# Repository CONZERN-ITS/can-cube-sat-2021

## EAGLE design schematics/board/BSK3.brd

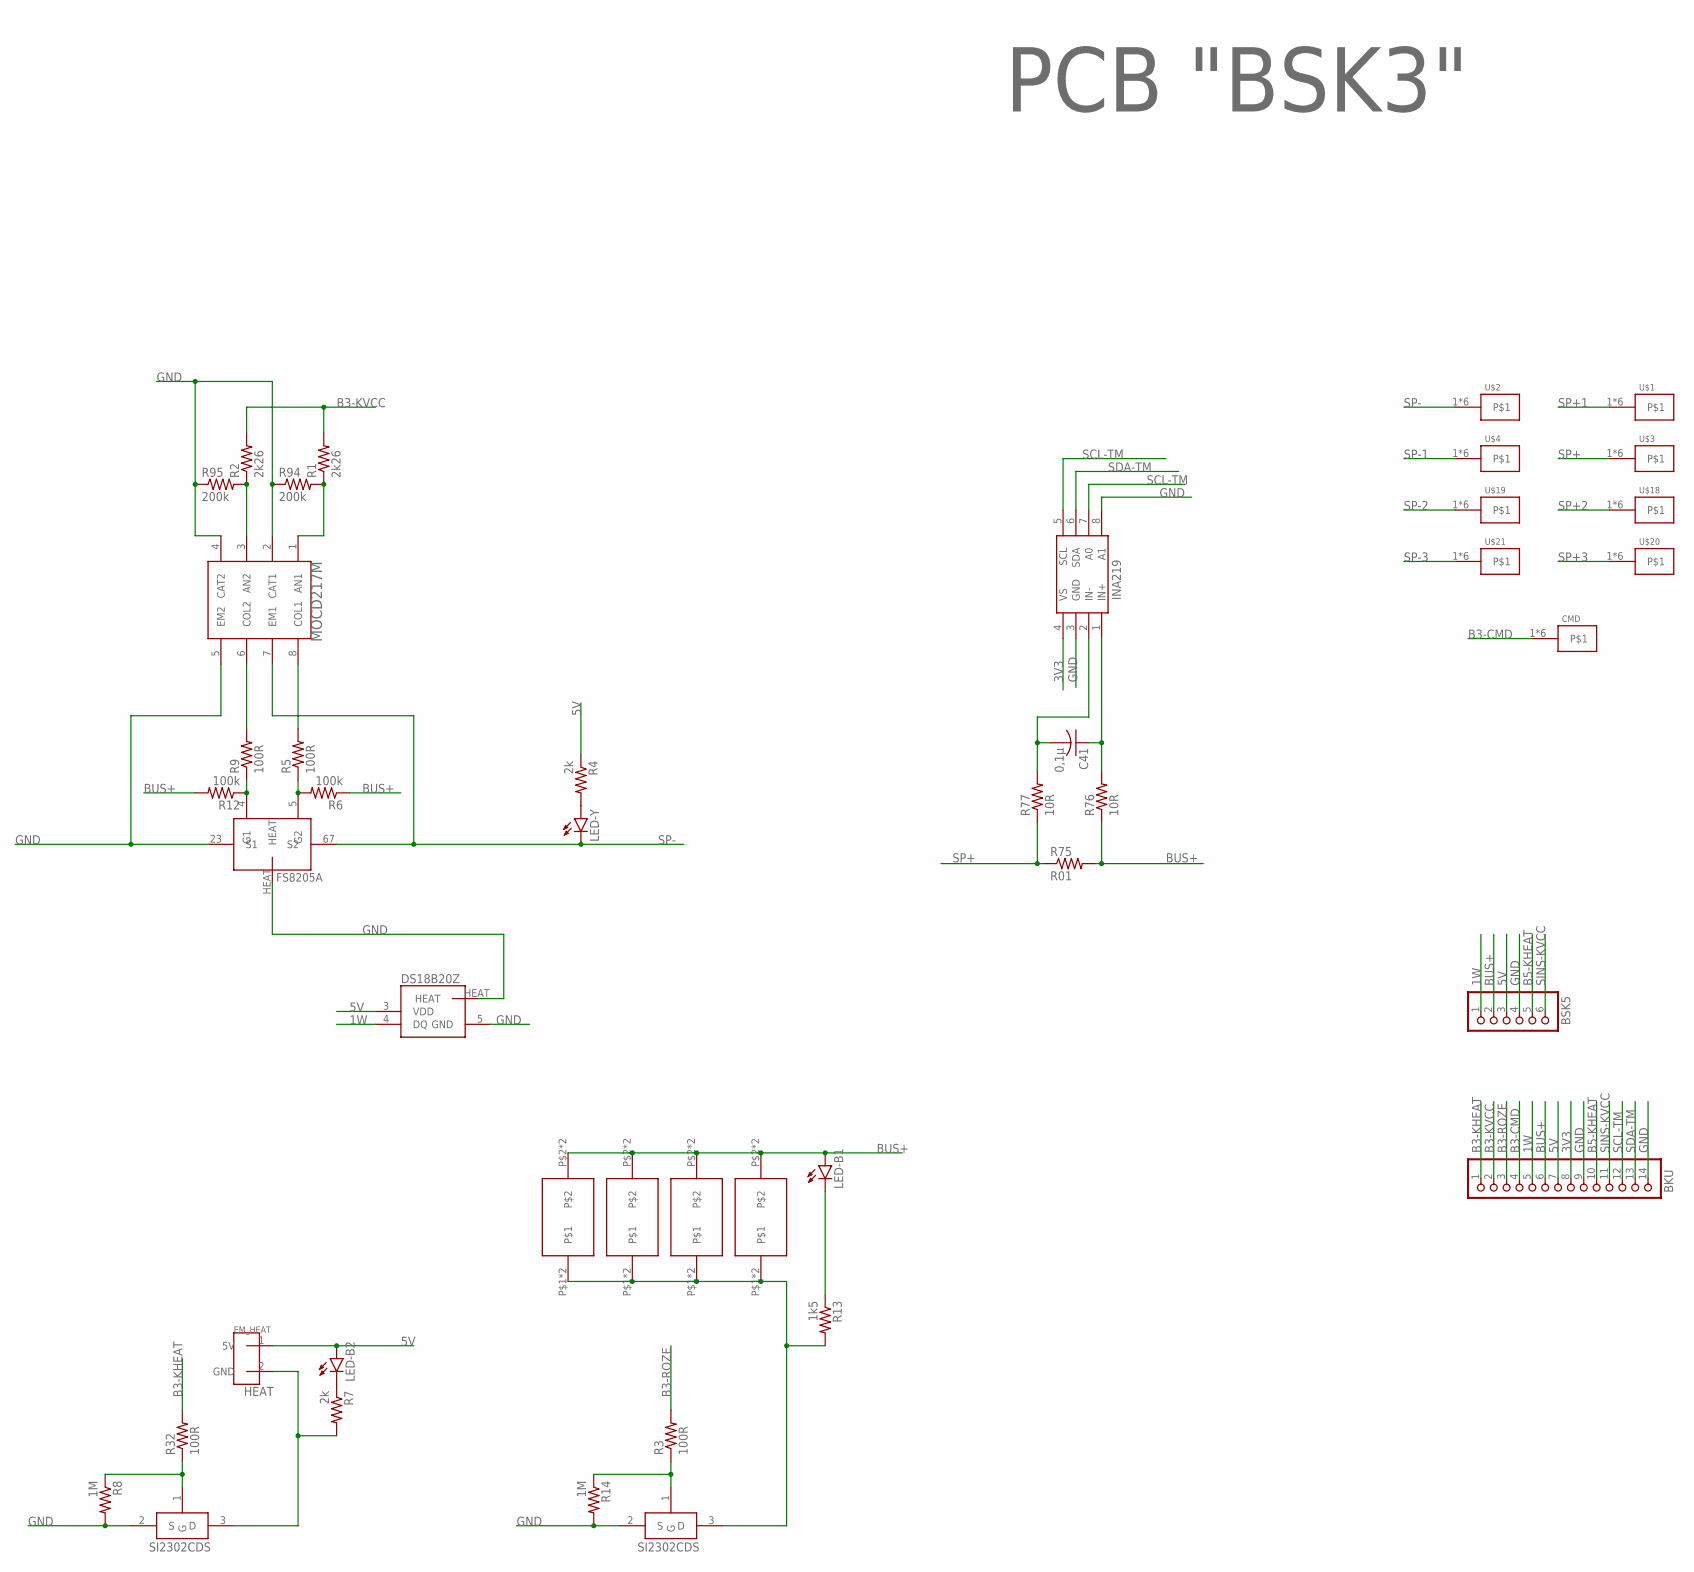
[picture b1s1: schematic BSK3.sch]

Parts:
BKU: PINHD-1X14; 1X14
BSK5: PINHD-1X6; 1X06
C41: 0,1µ; C0603
CMD: KCONNECTQUAD; KCONNECT_QUAD
DS18B20Z: DS18B20Z; SOIC8+HEAT_S
INA: INA219AID; SOT23-8
LED-B1, LED-B2: LEDCHIPLED_0603; CHIPLED_0603
LED-Y: LAP4-BOTTOM; P47F-BOTTOM
R1, R2: 2k26; R0603
R3, R5, R9, R32: 100R; R0603
R4, R7: 2k; R0603
R6, R12: 100k; R0603
R8, R14: 1M; R0603
R13: 1k5; R0603
R75: R01; R2512
R76, R77: 10R; R0603
R94, R95: 200k; R0603
U$1, U$2, U$3, U$4, U$18, U$19, U$20, U$21: KCONNECT
U$5: MOCD; SOIC8
U$6, U$7, U$15, U$16: GRAFITGRAFIT4_2; GRAFIT4_2
U$8, U$13: SI2302CDS; SOT23-3
U$9: PCB "BSK3"; ITS-LOGO
U$14: EM_HEAT
U$26: FS8205A+

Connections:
1: R7.2, U$8.3 (D), U$14.2 (GND)
1W: BKU.5, BSK5.1, DS18B20Z.4 (DQ)
2: R13.2, U$6.P$1, U$6.P$4, U$7.P$1, U$7.P$4, U$13.3 (D), U$15.P$1, U$15.P$4, U$16.P$1, U$16.P$4
3V3: BKU.8, INA.4 (VS)
5V: BKU.7, BSK5.3, DS18B20Z.3 (VDD), LED-B2.A, R4.1, U$14.1 (5V)
B3-CMD: BKU.4, CMD.1, CMD.2, CMD.3, CMD.4, CMD.P$1, CMD.P$2
B3-KHEAT: BKU.1, R32.2
B3-KVCC: BKU.2, R1.2, R2.2
B3-ROZE: BKU.3, R3.2
B5-KHEAT: BKU.10, BSK5.5
BUS+: BKU.6, BSK5.2, LED-B1.A, R6.1, R12.2, R75.2, R76.1, U$6.P$2, U$6.P$5, U$7.P$2, U$7.P$5, U$15.P$2, U$15.P$5, U$16.P$2, U$16.P$5
GND: BKU.9, BKU.14, BSK5.4, DS18B20Z.5 (GND), DS18B20Z.HEAT, INA.3 (GND), INA.8 (A1), R8.2, R14.2, R94.1, R95.1, U$5.2 (CAT1), U$5.4 (CAT2), U$5.5 (EM2), U$8.2 (S), U$13.2 (S), U$26.23 (S1), U$26.HEAT
unnamed: R5.1, R6.2, U$26.5 (G2)
unnamed: R1.1, R94.2, U$5.1 (AN1)
unnamed: R2.1, R95.2, U$5.3 (AN2)
unnamed: R8.1, R32.1, U$8.1 (G)
unnamed: R3.1, R14.1, U$13.1 (G)
unnamed: R9.1, R12.1, U$26.4 (G1)
unnamed: LED-Y.A, R4.2
unnamed: LED-B1.C, R13.1
unnamed: LED-B2.C, R7.1
unnamed: C41.1, INA.1 (IN+), R76.2
unnamed: C41.2, INA.2 (IN-), R77.2
OC1: R9.2, U$5.6 (COL2)
OD1: R5.2, U$5.8 (COL1)
SCL-TM: BKU.12, INA.5 (SCL), INA.7 (A0)
SDA-TM: BKU.13, INA.6 (SDA)
SINS-KVCC: BKU.11, BSK5.6
SP+: R75.1, R77.1, U$3.1, U$3.2, U$3.3, U$3.4, U$3.P$1, U$3.P$2
SP+1: U$1.1, U$1.2, U$1.3, U$1.4, U$1.P$1, U$1.P$2
SP+2: U$18.1, U$18.2, U$18.3, U$18.4, U$18.P$1, U$18.P$2
SP+3: U$20.1, U$20.2, U$20.3, U$20.4, U$20.P$1, U$20.P$2
SP-: LED-Y.C, U$2.1, U$2.2, U$2.3, U$2.4, U$2.P$1, U$2.P$2, U$5.7 (EM1), U$26.67 (S2)
SP-1: U$4.1, U$4.2, U$4.3, U$4.4, U$4.P$1, U$4.P$2
SP-2: U$19.1, U$19.2, U$19.3, U$19.4, U$19.P$1, U$19.P$2
SP-3: U$21.1, U$21.2, U$21.3, U$21.4, U$21.P$1, U$21.P$2

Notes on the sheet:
HEAT

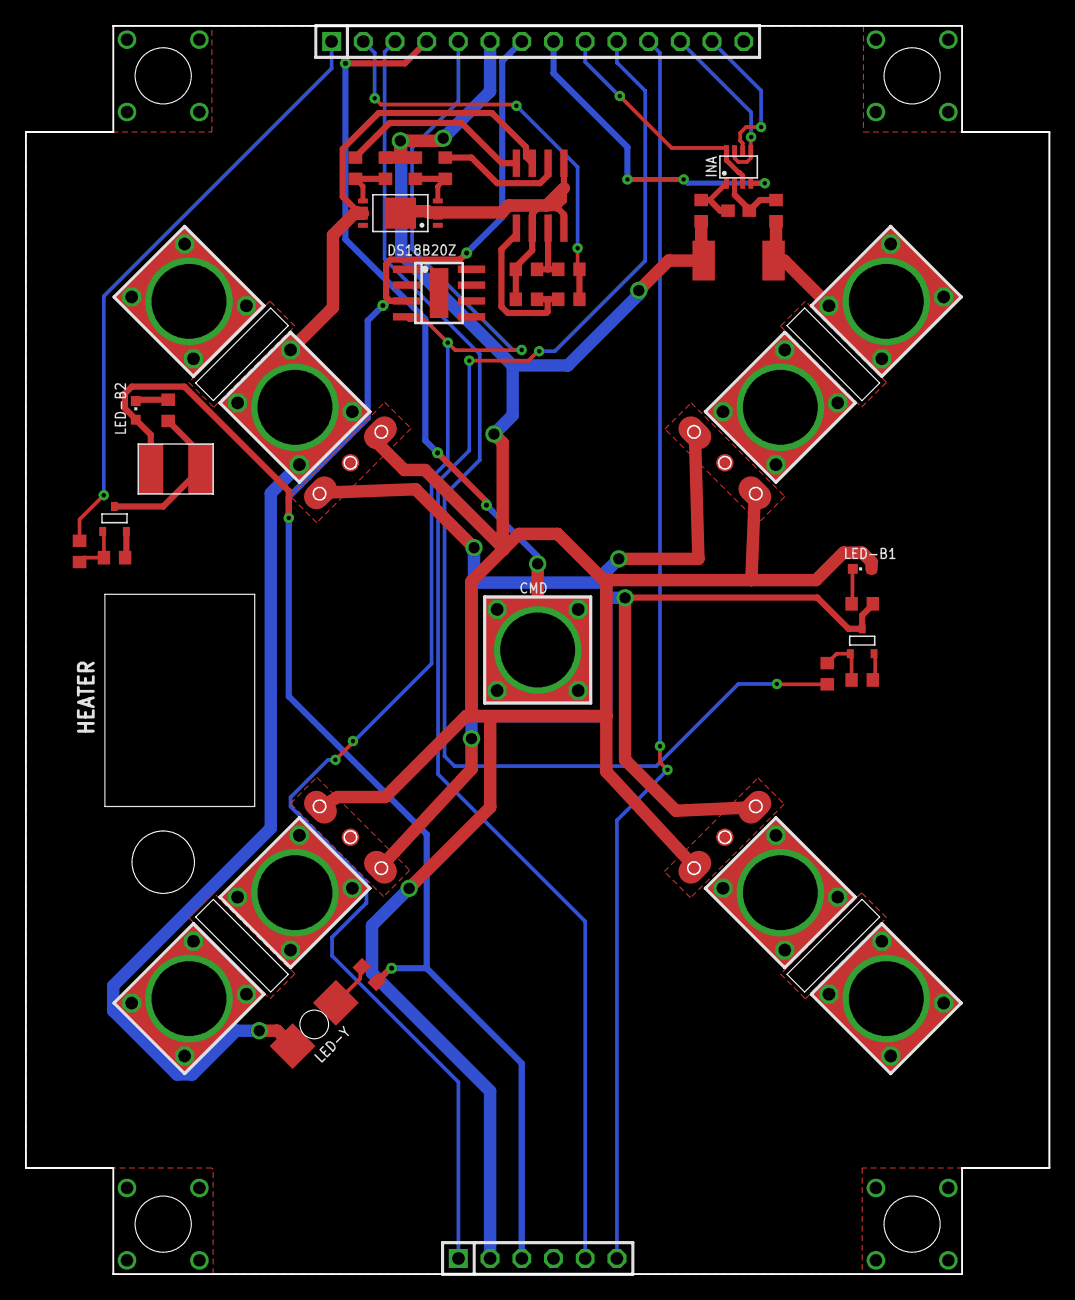
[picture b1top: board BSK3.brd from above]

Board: 2 copper layers, 82.0 x 100.0 mm, 45 parts (1 on the bottom side), 36 nets.

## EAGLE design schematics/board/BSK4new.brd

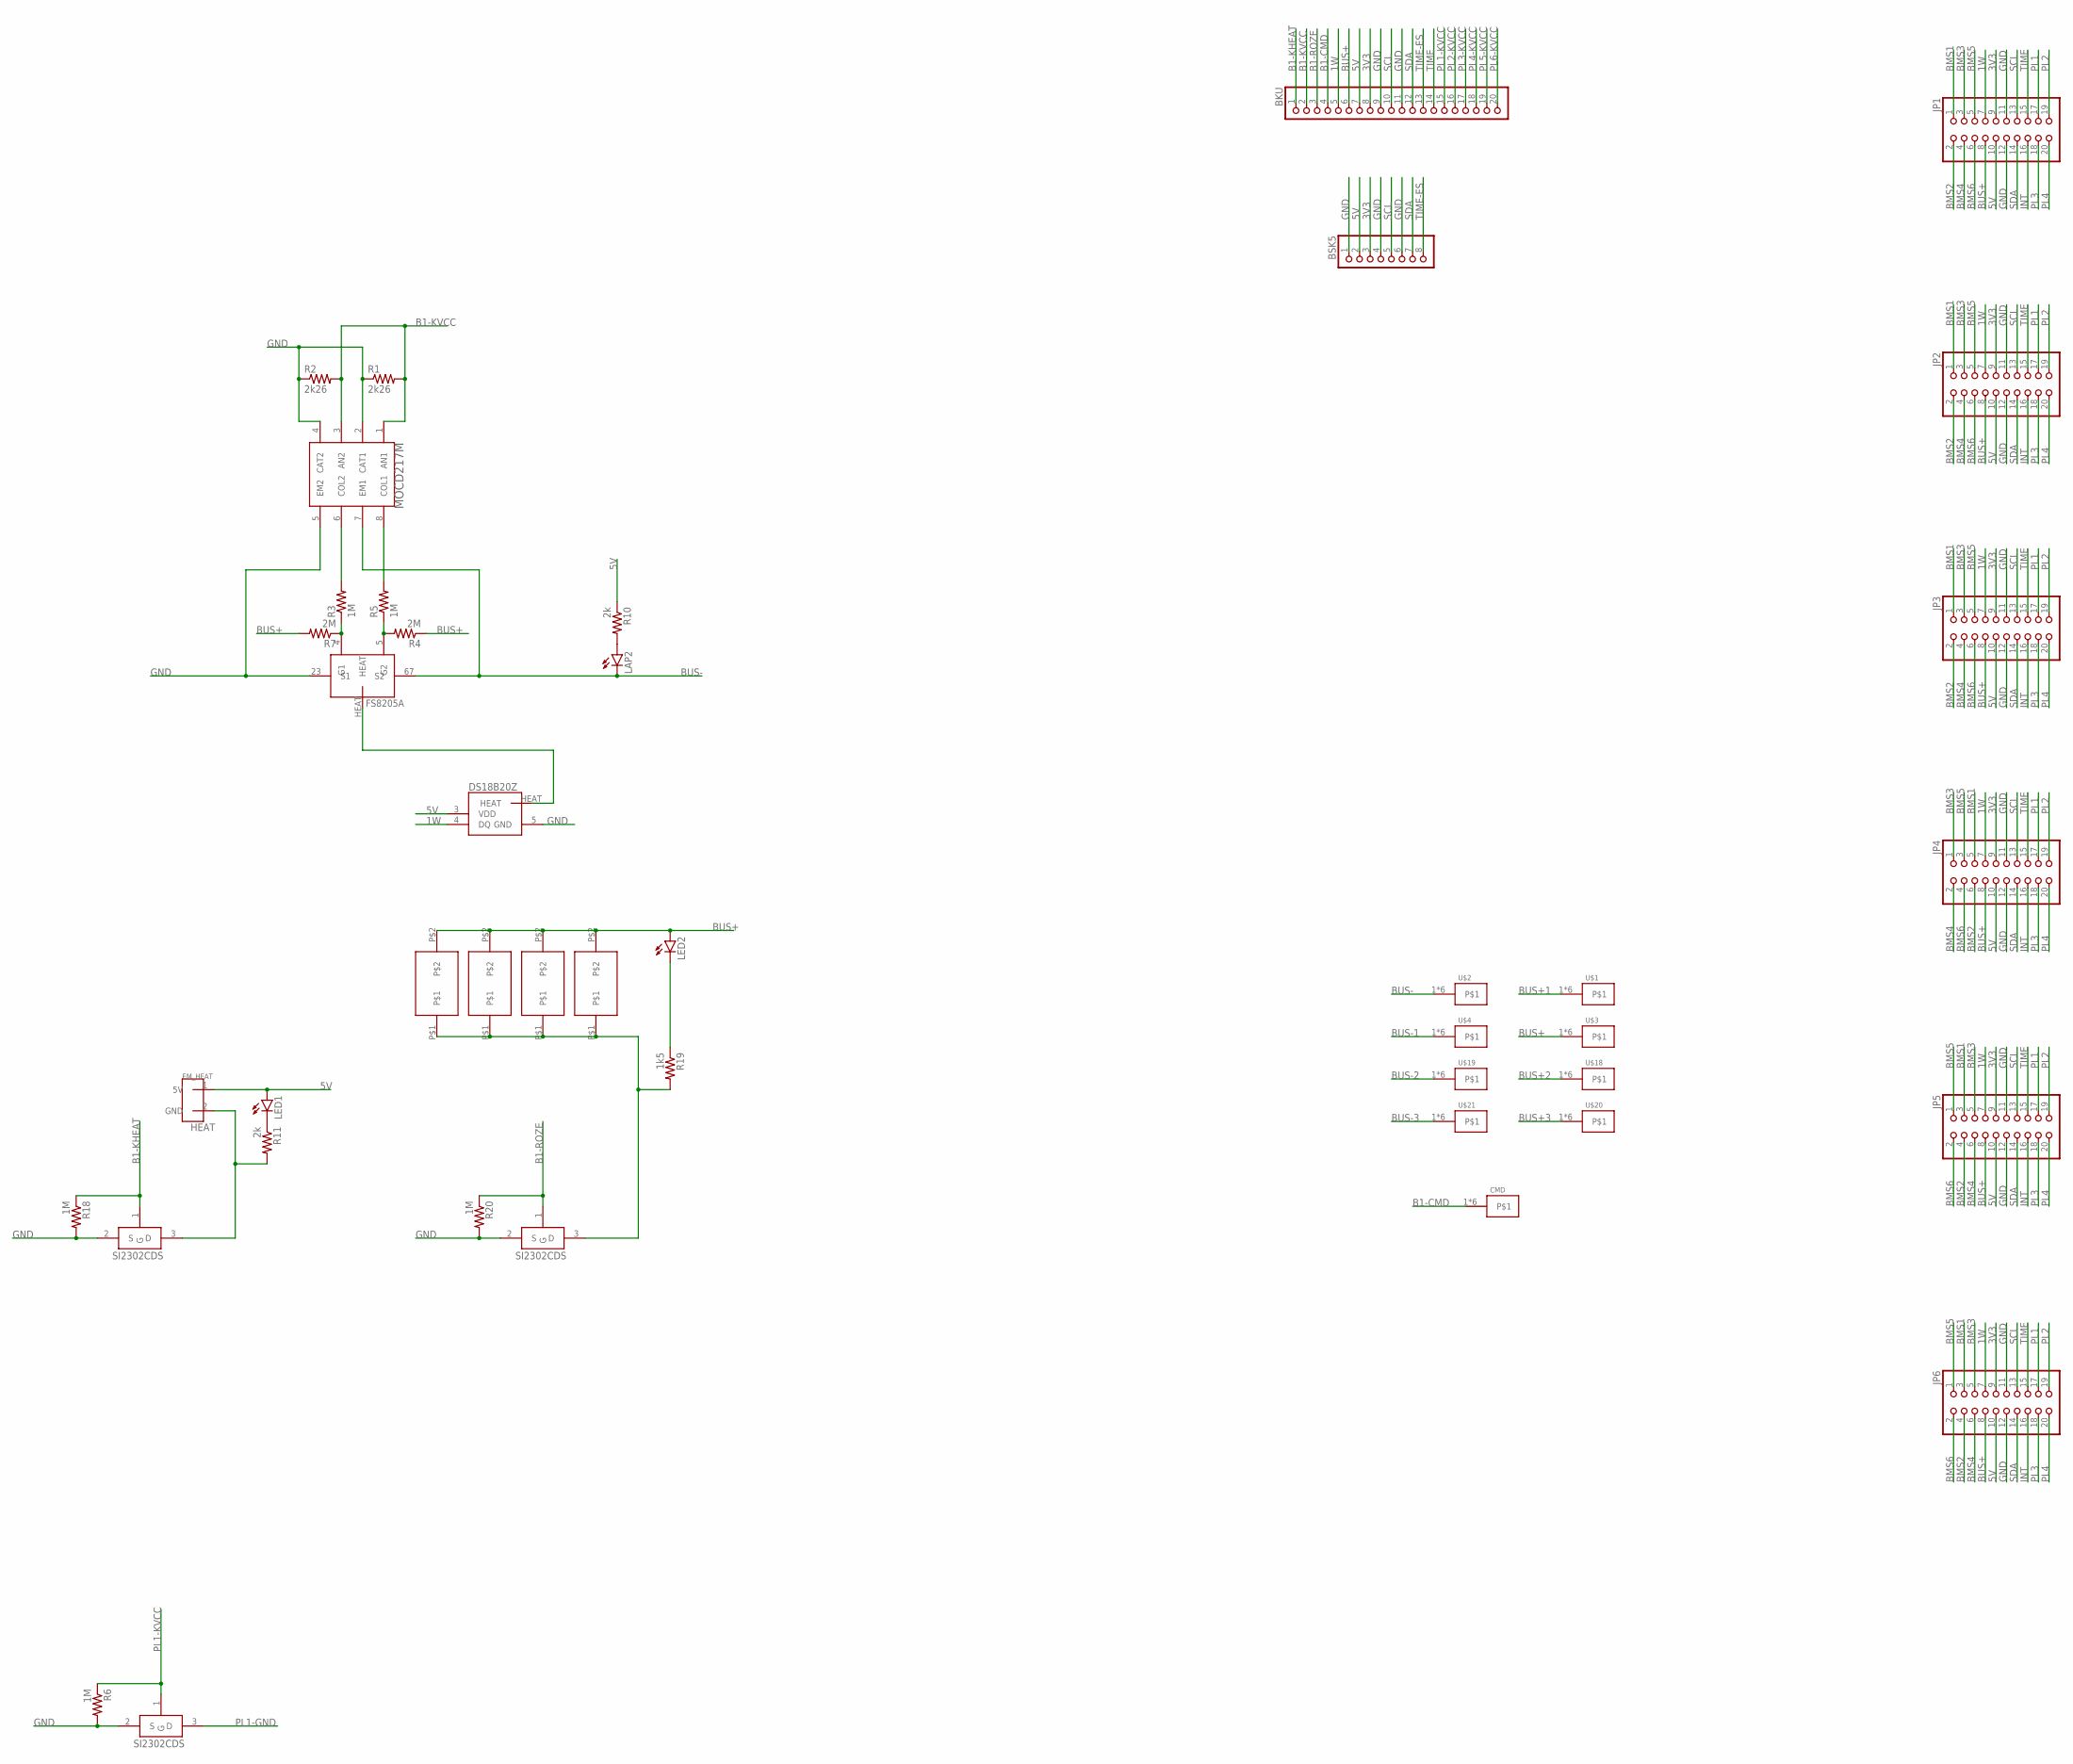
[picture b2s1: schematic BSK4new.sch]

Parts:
BKU: PINHD-1X20; 1X20
BSK5: PINHD-1X8; 1X08
CMD: KCONNECTQUAD; KCONNECT_QUAD
DS18B20Z: DS18B20Z
JP1, JP2, JP3, JP4, JP5, JP6: PINHD-2X10; 2X10
LAP2: LAP4-BOTTOM; P47F-BOTTOM
LED1, LED2: LEDCHIPLED_0603; CHIPLED_0603
R1, R2: 2k26; R0603
R3, R5, R6, R18, R20: 1M; R0603
R4, R7: 2M; R0603
R10, R11: 2k; R0603
R19: 1k5; R0603
U$1, U$2, U$3, U$4, U$18, U$19, U$20, U$21: KCONNECT
U$5, U$23, U$25: SI2302CDS; SOT23-3
U$17: FS8205A+
U$22: MOCD217M; SOIC8
U$24: EM_HEAT
U$27, U$28, U$29, U$30: GRAFITGRAFIT3_1; GRAFIT3_1

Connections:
1W: BKU.5, DS18B20Z.4 (DQ), JP1.7, JP2.7, JP3.7, JP4.7, JP5.7, JP6.7
3: R11.2, U$23.3 (D), U$24.2 (GND)
3V3: BKU.8, BSK5.3, JP1.9, JP2.9, JP3.9, JP4.9, JP5.9, JP6.9
4: R19.2, U$25.3 (D), U$27.P$1, U$28.P$1, U$29.P$1, U$30.P$1
5V: BKU.7, BSK5.2, DS18B20Z.3 (VDD), JP1.10, JP2.10, JP3.10, JP4.10, JP5.10, JP6.10, LED1.A, R10.1, U$24.1 (5V)
B1-CMD: BKU.4, CMD.1, CMD.2, CMD.3, CMD.4, CMD.P$1, CMD.P$2
B1-KHEAT: BKU.1, R18.1, U$23.1 (G)
B1-KVCC: BKU.2, R1.2, R2.2, U$22.1 (AN1), U$22.3 (AN2)
B1-ROZE: BKU.3, R20.1, U$25.1 (G)
BMS1: JP1.1, JP2.1, JP3.1, JP4.5, JP5.3, JP6.3
BMS2: JP1.2, JP2.2, JP3.2, JP4.6, JP5.4, JP6.4
BMS3: JP1.3, JP2.3, JP3.3, JP4.1, JP5.5, JP6.5
BMS4: JP1.4, JP2.4, JP3.4, JP4.2, JP5.6, JP6.6
BMS5: JP1.5, JP2.5, JP3.5, JP4.3, JP5.1, JP6.1
BMS6: JP1.6, JP2.6, JP3.6, JP4.4, JP5.2, JP6.2
BUS+: BKU.6, JP1.8, JP2.8, JP3.8, JP4.8, JP5.8, JP6.8, LED2.A, R4.1, R7.2, U$3.1, U$3.2, U$3.3, U$3.4, U$3.P$1, U$3.P$2, U$27.P$2, U$28.P$2, U$29.P$2, U$30.P$2
BUS+1: U$1.1, U$1.2, U$1.3, U$1.4, U$1.P$1, U$1.P$2
BUS+2: U$18.1, U$18.2, U$18.3, U$18.4, U$18.P$1, U$18.P$2
BUS+3: U$20.1, U$20.2, U$20.3, U$20.4, U$20.P$1, U$20.P$2
BUS-: LAP2.C, U$2.1, U$2.2, U$2.3, U$2.4, U$2.P$1, U$2.P$2, U$17.67 (S2), U$22.7 (EM1)
BUS-1: U$4.1, U$4.2, U$4.3, U$4.4, U$4.P$1, U$4.P$2
BUS-2: U$19.1, U$19.2, U$19.3, U$19.4, U$19.P$1, U$19.P$2
BUS-3: U$21.1, U$21.2, U$21.3, U$21.4, U$21.P$1, U$21.P$2
GND: BKU.9, BKU.11, BSK5.1, BSK5.4, BSK5.6, DS18B20Z.5 (GND), JP1.11, JP1.12, JP2.11, JP2.12, JP3.11, JP3.12, JP4.11, JP4.12, JP5.11, JP5.12, JP6.11, JP6.12, R1.1, R2.1, R6.2, R18.2, R20.2, U$5.2 (S), U$17.23 (S1), U$22.2 (CAT1), U$22.4 (CAT2), U$22.5 (EM2), U$23.2 (S), U$25.2 (S)
INT: JP1.16, JP2.16, JP3.16, JP4.16, JP5.16, JP6.16
unnamed: R4.2, R5.1, U$17.5 (G2)
unnamed: LED1.C, R11.1
unnamed: LED2.C, R19.1
unnamed: DS18B20Z.HEAT, U$17.HEAT
unnamed: R3.1, R7.1, U$17.4 (G1)
unnamed: LAP2.A, R10.2
OC2: R3.2, U$22.6 (COL2)
OD2: R5.2, U$22.8 (COL1)
PL1: JP1.17, JP2.17, JP3.17, JP4.17, JP5.17, JP6.17
PL1-GND: U$5.3 (D)
PL1-KVCC: BKU.15, R6.1, U$5.1 (G)
PL2: JP1.19, JP2.19, JP3.19, JP4.19, JP5.19, JP6.19
PL2-KVCC: BKU.16
PL3: JP1.18, JP2.18, JP3.18, JP4.18, JP5.18, JP6.18
PL3-KVCC: BKU.17
PL4: JP1.20, JP2.20, JP3.20, JP4.20, JP5.20, JP6.20
PL4-KVCC: BKU.18
PL5-KVCC: BKU.19
PL6-KVCC: BKU.20
SCL: BKU.10, BSK5.5, JP1.13, JP2.13, JP3.13, JP4.13, JP5.13, JP6.13
SDA: BKU.12, BSK5.7, JP1.14, JP2.14, JP3.14, JP4.14, JP5.14, JP6.14
TIME: BKU.14, JP1.15, JP2.15, JP3.15, JP4.15, JP5.15, JP6.15
TIME-ES: BKU.13, BSK5.8

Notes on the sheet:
HEAT

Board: 2 copper layers, 43 parts (6 on the bottom side), 42 nets, no tracks yet.

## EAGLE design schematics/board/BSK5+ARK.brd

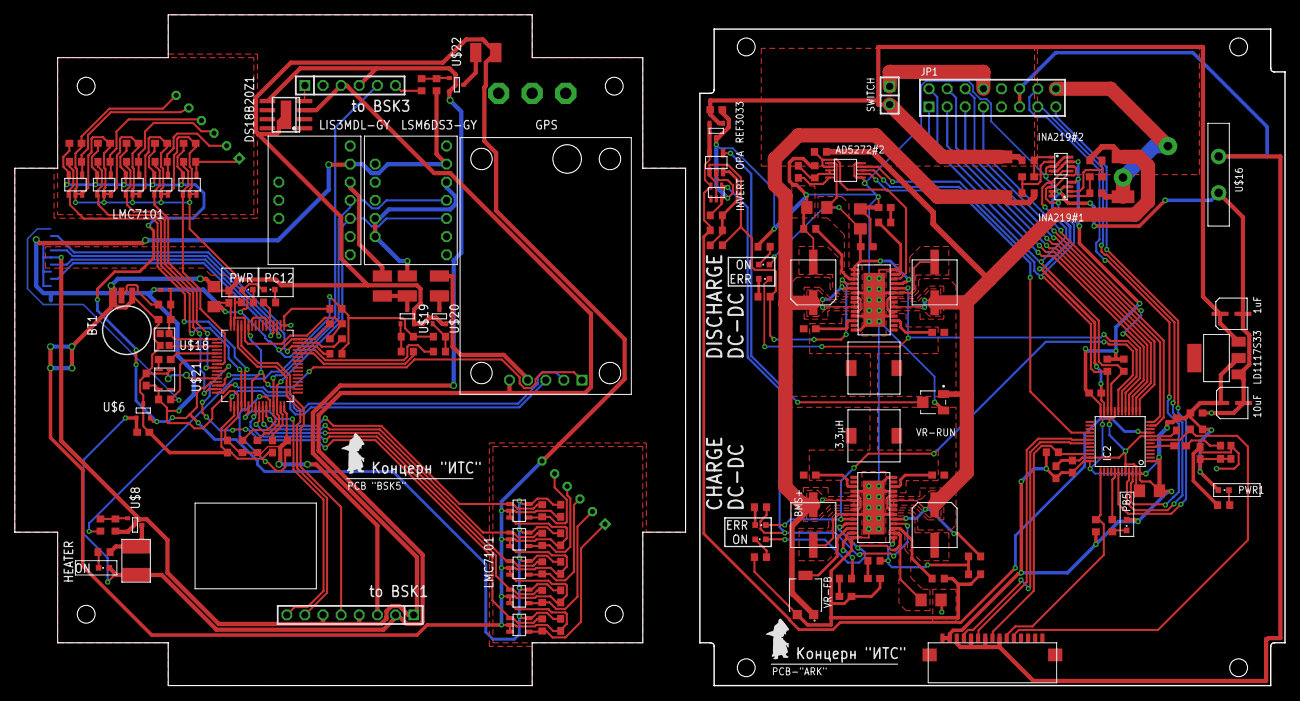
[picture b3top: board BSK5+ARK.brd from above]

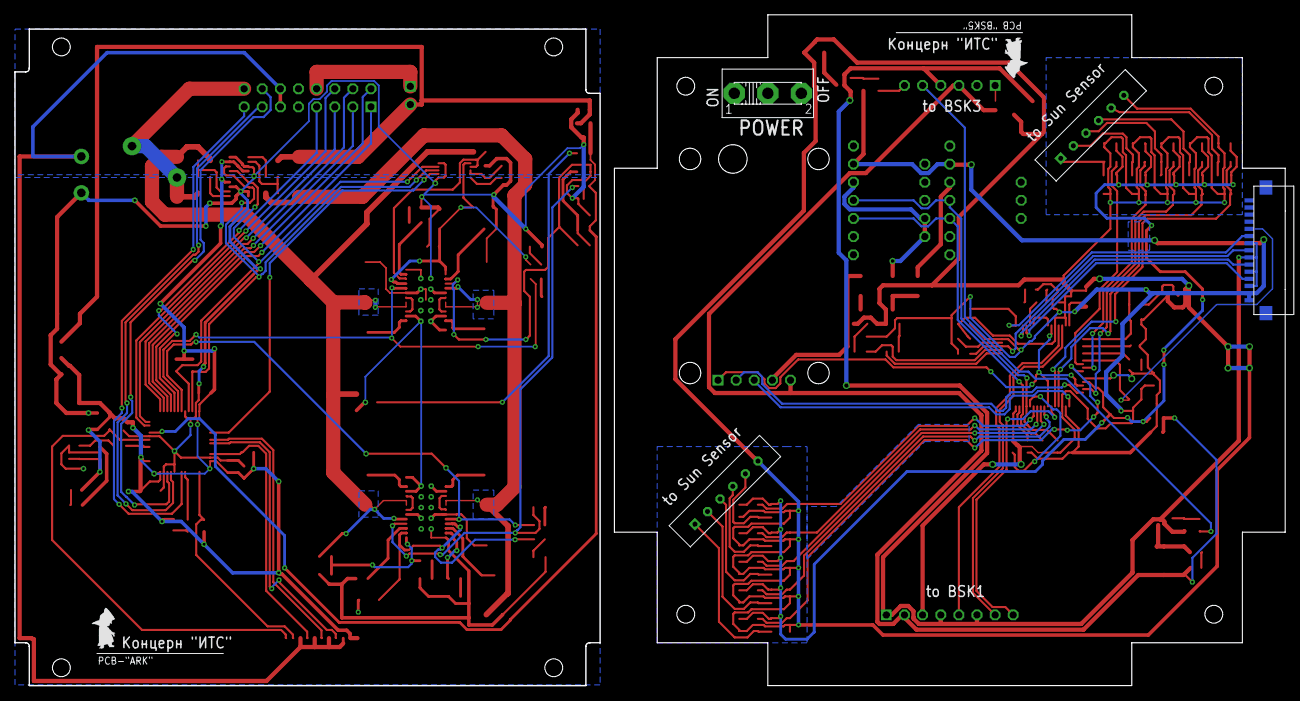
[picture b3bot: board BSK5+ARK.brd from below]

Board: 2 copper layers, 178.0 x 94.0 mm, 173 parts (6 on the bottom side), 134 nets.

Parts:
3,3µH: 3,3µ; B82472G6
3,3µH1: 3,3µH; B82472G6
AD5272#2: AD5272; MSOP10
BSK1: 1X08
BSK3: 1X06
BT1: 6.8MM_COIN_CELL; BATTCON-6.8MM
C1, C5, C31: 10nF; C0603
C2, C6, C7, C8, C11, C12, C14, C15, C16, C17, C18, C20, C22, C23, C25, C26, C27, C54, C55: 100nF; C0603
C3, C33: 470nF; C0603
C4, C30: 1nF; C0603
C9, C13: 2,2µ; C0603
C10, C47: 150µ; ECAP150-CMD
C19, C24, C57: 10µ; C1206
C21, C48: 220µ; ECAP220-CMD
C28, C29, C40, C41, C49, C50, C56: 0,1µ; C0603
C32: 1µ; C0603
C34: 10uF; ECAP-SMD-D4
C35: 1uF; ECAP-SMD-D4
C44, C52: 680p; C0603
C45, C53: 4.7µ; C1206
C46: 3,3n; C0603
D1: BB141; SOD523
DS18B20Z1: DS18B20Z; SOIC8+HEAT_S
GPS: GPSNEO6M; GPS-NEO6M
HEATER: EM_HEAT
IC2: STM32F103C8T; LQFP48
INA219#1, INA219#2: INA219AID; SOT23-8
INVERT: INVERTER.; SC70
JP1: 2X08
LD1117S33: LD1117S33; SOT223
LED_G1, LED_G2: CHIPLED_0603
LED_R1, LED_R2: CHIPLED_0603
LIS3MDL-GY: LIS3MDL-GY
LSM6DS3-GY: LSM6DS3-GY
ON: CHIPLED_0603
OPA: OPA333; SOT23-5
PB5: CHIPLED_0603
PC12: CHIPLED_0603
PWR, PWR1: CHIPLED_0603
R1, R2, R3, R36, R64, R66, R79: 10k; R0603
R4, R5, R6, R9, R12, R13, R14, R18, R19, R28: 24k9; R0603
R7, R15, R16, R27, R35, R57, R81, R82, R100: 2k; R0603
R8, R22, R24, R33, R65: 1M; R0603
R10: 620R; R0603
R11, R17, R67, R68, R69: 150k; R0603
R20: 0.5A; R1210
R21: 0.2A; R1210
R23, R34: 0.05A; R1210
R25, R26, R101, R102: 5k1; R0603
R29, R30, R31, R32: 100R; R0603
R37: 14K3; R0603
R38: 91K; R0603
R39: 430k; R0603
R40: 680k; R0603
R41: 120k; R0603
R71, R75: R01; R2512
R73, R74, R76, R77: 10R; R0603
REF3033: REF3033; SOT23-3
S1: UNICS-SWITCH
SWITCH: 1X02
TCXO: OC2E08000XCCDRX
U1: STM32F405RGT6; QFP50P1200X1200X160-64N
U$1, U$2, U$3, U$4, U$5, U$7, U$9, U$10, U$11, U$23: LMC7101
U$6: REF3033; SOT23-3
U$8, U$19, U$20, U$22: SI2302CDS; SOT23-3
U$12, U$15: FFC-CONNECT68611; 68611
U$13, U$26: PCB "BSK5"; ITS-LOGO
U$14, U$59: LTC31191; LTC3119+VIA
U$16: MF-R400
U$17, U$24: PCB-"ARK"; ITS-LOGO
U$18: Q32.768
U$21: Q24
VR-FB: 3314G-1-504E; TRIM_3314G-1-504E
VR-RUN: 3313J-1-205E; TRIM_3313J-1-205E
X1, X11: JST-6A; B6B-EH-A

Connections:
1: HEATER.2, R7.2, U$8.3
1W: BSK3.1, DS18B20Z1.4
1W1: IC2.17, JP1.7
3V1: C22.1, C23.1, C24.1, C25.1, C26.1, C27.1, C31.2, C34.P+, IC2.1, IC2.24, IC2.36, IC2.48, INA219#1.4, INA219#2.4, INA219#2.7, LD1117S33.P$3, PB5.A, PWR1.A, R36.1, R64.1, R79.1, R101.1, R102.1, TCXO.P$1, TCXO.P$4, U$15.P$1, U$15.P$2
3V3: BSK1.3, C5.2, C18.2, C19.2, C20.2, C54.2, C55.2, D1.A, LIS3MDL-GY.P$6, LSM6DS3-GY.P$6, PC12.A, PWR.A, R1.2, R2.2, R3.2, R22.1, R24.1, R25.1, R26.1, R33.1, U1.19, U1.32, U1.48, U1.64, U$12.P$1, U$12.P$2, U$21.P$4
3V3-STAB: C2.1, C6.1, C7.1, C8.1, C11.1, C12.1, C14.1, C15.1, C16.1, C17.1, U1.13, U$1.P$5, U$2.P$5, U$3.P$5, U$4.P$5, U$5.P$5, U$6.2, U$7.P$5, U$9.P$5, U$10.P$5, U$11.P$5, U$23.P$5
3V3-STAB1: IC2.9, INVERT.P$5, OPA.P$5, R41.1, REF3033.2
5V: BSK1.2, BSK3.3, C3.2, DS18B20Z1.3, GPS.P$5, HEATER.1, ON.A, U$6.1
90: R65.1, R66.2, R67.2, U$59.15
A: INVERT.P$2, OPA.P$1, R35.1, R40.1, U$14.18
B5-KHEAT: BSK3.5, R29.1
BMS1: IC2.16, JP1.1
BMS2: IC2.15, JP1.2
BMS3: IC2.14, JP1.3
BMS4: IC2.13, JP1.4
BMS5: IC2.12, JP1.5
BMS6: IC2.11, JP1.6
BMS+: C33.2, C35.P+, LD1117S33.P$4, R75.2, R76.1, REF3033.1, SWITCH.2
BMS+_OUT: JP1.8, SWITCH.1
BUS+1: JP1.16, R71.2, R73.1
CELL: C1.2, D1.C, R10.2, U1.1, U$18.P$4
DPD_RST: AD5272#2.7, IC2.28
GND: BT1.-, C1.1, C2.2, C3.1, C5.1, C6.2, C7.2, C8.2, C9.1, C11.2, C12.2, C13.1, C14.2, C15.2, C16.2, C17.2, C18.1, C19.1, C20.1, C54.1, C55.1, DS18B20Z1.HEAT, R16.1, R20.2, U1.12, U1.18, U1.28, U1.60, U1.63, U$1.P$2, U$1.P$3, U$2.P$2, U$2.P$3, U$3.P$2, U$3.P$3, U$4.P$2, U$4.P$3, U$5.P$2, U$5.P$3, U$6.3, U$7.P$2, U$7.P$3, U$9.P$2, U$9.P$3, U$10.P$2, U$10.P$3, U$11.P$2, U$11.P$3, U$18.P$2, U$19.2, U$20.2, U$21.P$2, U$23.P$2, U$23.P$3, X1.6, X11.6
GND1: AD5272#2.6, AD5272#2.10, C10.P$2, C21.P$2, C22.2, C23.2, C24.2, C25.2, C26.2, C27.2, C31.1, C33.1, C34.P-, C35.P-, C44.2, C45.2, C46.2, C47.P$2, C48.P$2, C52.2, C53.2, C56.2, C57.2, IC2.8, IC2.20, IC2.23, IC2.35, IC2.44, IC2.47, INA219#1.3, INA219#1.7, INA219#1.8, INA219#2.3, INA219#2.8, INVERT.P$3, LD1117S33.P$2, OPA.P$2, R11.1, R27.1, R37.2, R39.1, R67.1, R68.1, R82.1, R100.1, REF3033.3, TCXO.P$2, U$14.4, U$14.9, U$14.14, U$14.20, U$14.25, U$14.28, U$14.29, U$14.P$1, U$14.P$2, U$14.P$3, U$14.P$4, U$14.P$5, U$14.P$6, U$14.P$7, U$14.P$8, U$14.P$9, U$14.P$10, U$16.P$1, U$59.4, U$59.9, U$59.14, U$59.20, U$59.25, U$59.28, U$59.29, U$59.P$1, U$59.P$2, U$59.P$3, U$59.P$4, U$59.P$5, U$59.P$6, U$59.P$7, U$59.P$8, U$59.P$9, U$59.P$10, VR-FB.3, VR-RUN.3
GND-GPS: R21.2, U$20.3
GND-MAG: R23.2, R34.2, U$19.3
GND-OUT: BSK1.1, BSK1.4, BSK1.6, BSK3.4, DS18B20Z1.5, R8.2, U$8.2, U$12.P$3, U$12.P$5, U$12.P$7, U$12.P$9, U$22.2
GND-OUT1: JP1.11, JP1.12, U$15.P$3, U$15.P$5, U$15.P$7, U$15.P$9, U$16.P$2
GPS: R32.1, U1.45
INA_BMS+: C21.P$1, C47.P$1, R75.1, R77.1, U$14.19, U$14.22, U$14.23, U$59.6, U$59.7, VR-FB.1
INA_BUS+: C10.P$1, C48.P$1, R38.1, R65.2, R71.1, R74.1, U$14.6, U$14.7, U$59.19, U$59.22, U$59.23, VR-RUN.1
MAG: R31.1, U1.44
unnamed: U1.3, U$18.P$3
unnamed: R20.1, U$22.3
unnamed: C28.2, INA219#1.2, R74.2
unnamed: R13.1, U$7.P$4, X11.1
unnamed: R6.1, U$3.P$4, X1.1
unnamed: R9.1, U$4.P$4, X1.4
unnamed: R8.1, R29.2, U$8.1
unnamed: C30.2, TCXO.P$3
unnamed: C30.1, IC2.5
unnamed: R30.2, R33.2, U$22.1
unnamed: R24.2, R31.2, U$19.1
unnamed: LSM6DS3-GY.P$5, LSM6DS3-GY.P$8, LSM6DS3-GY.P$9, R23.1
unnamed: R22.2, R32.2, U$20.1
unnamed: LIS3MDL-GY.P$5, R34.1
unnamed: AD5272#2.3, AD5272#2.4, C32.2, R37.1
unnamed: AD5272#2.2, R38.2, U$14.12
unnamed: PB5.C, R81.2
unnamed: OPA.P$3, R39.2, R40.2, R41.2
unnamed: BT1.+, R10.1
unnamed: GPS.P$4, R21.1
unnamed: U1.54, U1.58
unnamed: C13.2, U1.47
unnamed: R4.1, U$1.P$4, X11.4
unnamed: R5.1, U$2.P$4, X11.5
unnamed: ON.C, R7.1
unnamed: R12.1, U$5.P$4, X1.5
unnamed: C9.2, U1.31
unnamed: PC12.C, R15.2
unnamed: R15.1, U1.53
unnamed: PWR.C, R16.2
unnamed: GPS.P$2, U1.16
unnamed: GPS.P$3, U1.17
unnamed: C4.2, U$21.P$3
unnamed: C4.1, U1.5
unnamed: R28.1, U$23.P$4, X11.3
unnamed: R14.1, U$9.P$4, X11.2
unnamed: R18.1, U$10.P$4, X1.2
unnamed: R19.1, U$11.P$4, X1.3
unnamed: AD5272#2.5, C32.1
unnamed: 3,3µH1.2, C49.1, U$14.21, U$14.24
unnamed: 3,3µH1.1, C50.1, U$14.5, U$14.8
unnamed: R11.2, U$14.17
unnamed: C49.2, U$14.26
unnamed: R17.1, U$14.13
unnamed: C52.1, R17.2
unnamed: C50.2, U$14.3
unnamed: LED_R1.A, R35.2
unnamed: LED_R2.A, R57.2
unnamed: U$59.12, VR-FB.2
unnamed: LED_G1.C, R100.2
unnamed: LED_G2.C, R27.2
unnamed: C41.2, U$59.3
unnamed: 3,3µH.2, C40.1, U$59.21, U$59.24
unnamed: 3,3µH.1, C41.1, U$59.5, U$59.8
unnamed: R69.1, U$59.13
unnamed: C44.1, R69.2
unnamed: C46.1, R66.1
unnamed: R68.2, U$59.17
unnamed: C40.2, U$59.26
unnamed: C28.1, INA219#1.1, R73.2
unnamed: C29.1, INA219#2.1, R76.2
unnamed: C29.2, INA219#2.2, R77.2
unnamed: PWR1.C, R82.2
unnamed: IC2.41, R81.1
unnamed: AD5272#2.1, C53.1, C56.1, C57.1, LED_G2.A, U$14.11, U$14.15, U$14.16
unnamed: C45.1, LED_G1.A, U$59.11, U$59.16
NRST: R1.1, U1.7, U$12.P$11
NRST1: IC2.7, R79.2, U$15.P$11
PGOOD1: IC2.19, LED_R2.C, U$59.10
PGOOD2: IC2.18, LED_R1.C, U$14.10
RUN: OPA.P$4, VR-RUN.2
RX-S: U1.52, U$12.P$4
RX-S1: IC2.31, U$15.P$4
SCL: LIS3MDL-GY.P$4, LSM6DS3-GY.P$4, R25.2, U1.29
SCL1: AD5272#2.9, IC2.21, INA219#1.5, INA219#2.5, R101.2
SCL-TM: BSK1.5, U1.61
SCLTM: IC2.45, JP1.13
SDA: LIS3MDL-GY.P$3, LSM6DS3-GY.P$3, R26.2, U1.30
SDA1: AD5272#2.8, IC2.22, INA219#1.6, INA219#2.6, R102.2
SDA-TM: BSK1.7, U1.62
SDATM: IC2.46, JP1.14
SINS-KVCC: BSK3.6, R30.1
SS1: R28.2, U1.15, U$23.P$1
SS2: R4.2, U1.20, U$1.P$1
SS3: R5.2, U1.21, U$2.P$1
SS4: R6.2, U1.10, U$3.P$1
SS5: R9.2, U1.26, U$4.P$1
SS6: R12.2, U1.27, U$5.P$1
SS7: R13.2, U1.8, U$7.P$1
SS8: R14.2, U1.9, U$9.P$1
SS9: R18.2, U1.24, U$10.P$1
SS10: R19.2, U1.25, U$11.P$1
SWC: R3.1, U1.49, U$12.P$10
SWC1: IC2.37, R36.2, U$15.P$10
SWD: R2.1, U1.46, U$12.P$8
SWD1: IC2.34, R64.2, U$15.P$8
TIME: IC2.42, JP1.15
TIME-ES: BSK1.8, U1.22
TIME-G: GPS.P$1, U1.14, U1.23, U1.59
TX-S: U1.51, U$12.P$6
TX-S1: IC2.30, U$15.P$6
Y: INVERT.P$4, R57.1, U$59.18

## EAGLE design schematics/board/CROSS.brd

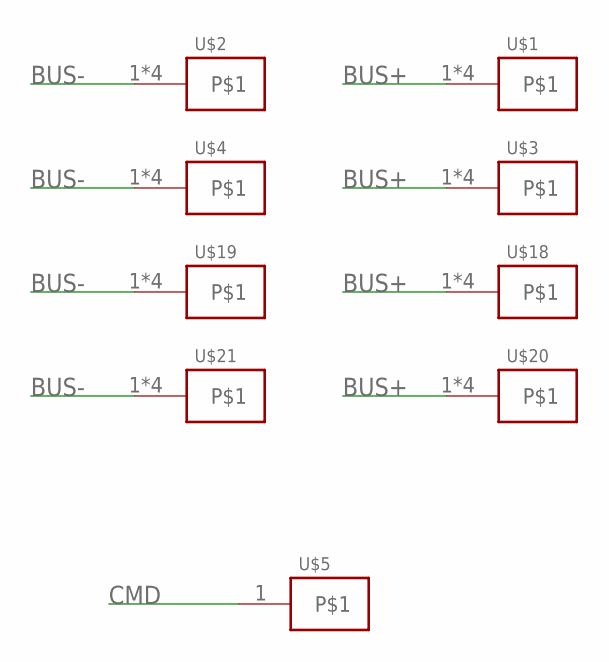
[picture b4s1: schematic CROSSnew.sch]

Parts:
U$1, U$2, U$3, U$4, U$18, U$19, U$20, U$21: KCONNECT-
U$5: KCONNECTQUAD-; KCONNECT-_QUAD

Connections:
BUS+: U$1.1, U$1.2, U$1.3, U$1.4, U$3.1, U$3.2, U$3.3, U$3.4, U$18.1, U$18.2, U$18.3, U$18.4, U$20.1, U$20.2, U$20.3, U$20.4
BUS-: U$2.1, U$2.2, U$2.3, U$2.4, U$4.1, U$4.2, U$4.3, U$4.4, U$19.1, U$19.2, U$19.3, U$19.4, U$21.1, U$21.2, U$21.3, U$21.4
CMD: U$5.1, U$5.2, U$5.3, U$5.4

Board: 2 copper layers, 9 parts (0 on the bottom side), 3 nets, no tracks yet.

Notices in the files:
parts and their libraries:
SparkFun-Batteries: Licensing: Creative Commons ShareAlike 4.0 International - https://creativecommons.org/licenses/by-sa/4.0
